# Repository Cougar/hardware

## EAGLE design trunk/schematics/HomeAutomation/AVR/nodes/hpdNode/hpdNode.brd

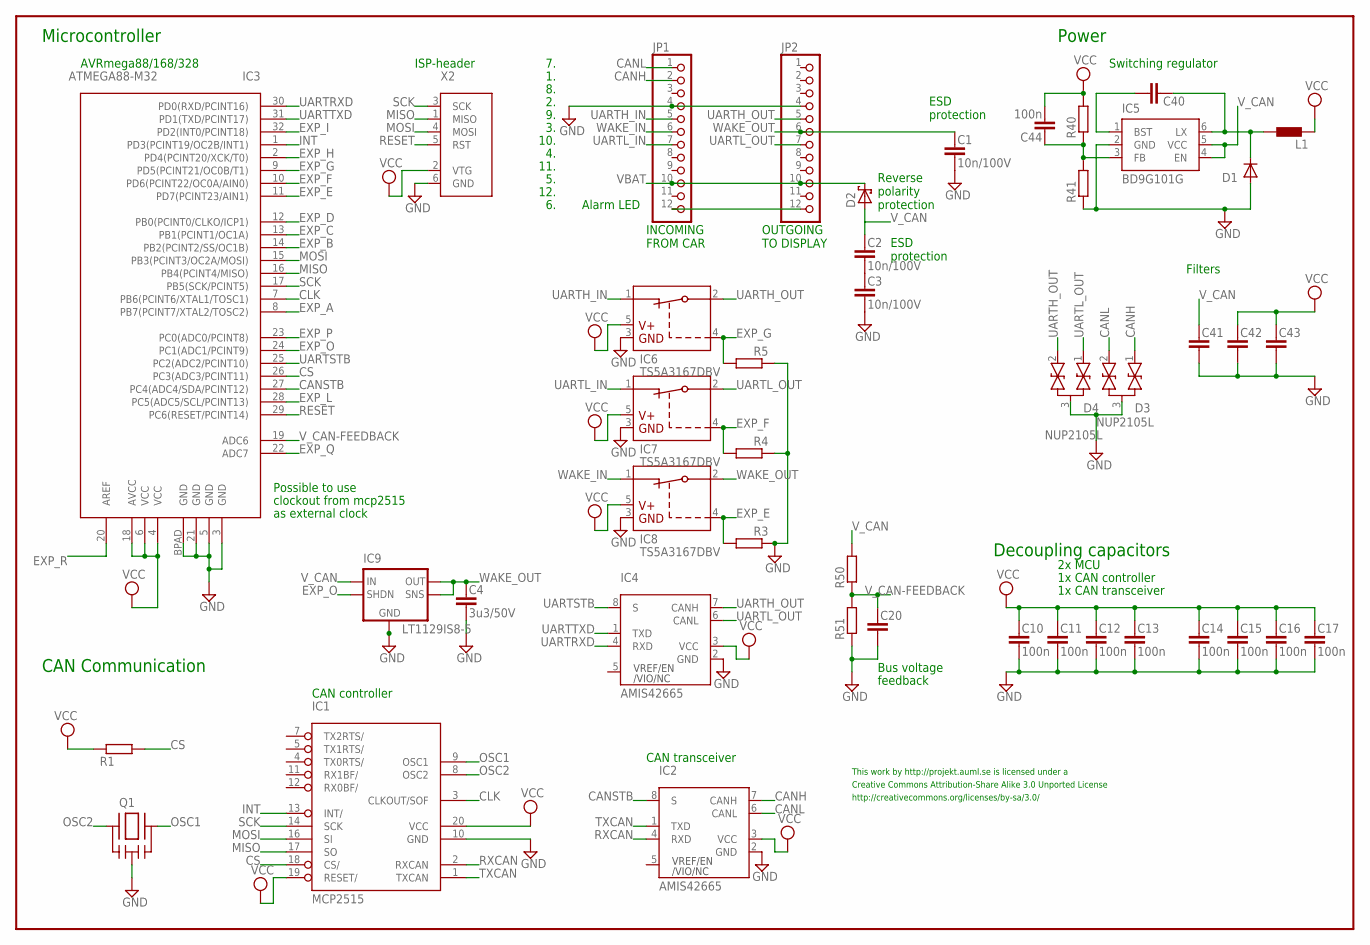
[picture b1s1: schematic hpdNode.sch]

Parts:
C1, C2, C3: 10n/100V; C0805
C4: 3u3/50V; C1210
C10, C11, C12, C13, C14, C15, C16, C17, C44: 100n; C0402
C20, C43: C-EUC0402; C0402
C40: C-EUC0603; C0603
C41: C-EUC1210; C1210
C42: C-EUC0805; C0805
D1: DIODESMP; DO-220AA
D2: SCHOTTKY-DIODESMA; SMA
D3, D4: NUP2105L; SOT23
IC1: MCP2515; TSSOP
IC2, IC4: AMIS42665; SOIC
IC3: ATMEGA88-M32; MLF32
IC5: BD9G101G; SSOP6
IC6, IC7, IC8: TS5A3167DBV; SOT23-5
IC9: LT1129IS8-5; SO8
JP1, JP2: PINHD-2X06; 2X06
L1: L-EUL1210; L1210
Q1: CSTCESMD; SMD
R1, R3, R4, R5, R40, R41, R50, R51: R-EUR0402; R0402
X2: AVRISP6PINHEADER; 6PINHEADER

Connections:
CANH: D3.1, IC2.7 (CANH), JP1.2
CANL: D3.2, IC2.6 (CANL), JP1.1
CANSTB: IC2.8 (S), IC3.27 (PC4(ADC4/SDA/PCINT12))
CB: C40.1, IC5.1 (BST)
CLK: IC1.3 (CLKOUT/SOF), IC3.7 (PB6(PCINT6/XTAL1/TOSC1))
CS: IC1.18 (CS/), IC3.26 (PC3(ADC3/PCINT11)), R1.2
EXP_A: IC3.8 (PB7(PCINT7/XTAL2/TOSC2))
EXP_B: IC3.14 (PB2(PCINT2/SS/OC1B))
EXP_C: IC3.13 (PB1(PCINT1/OC1A))
EXP_D: IC3.12 (PB0(PCINT0/CLKO/ICP1))
EXP_E: IC3.11 (PD7(PCINT23/AIN1)), IC8.4 (IN), R3.2
EXP_F: IC3.10 (PD6(PCINT22/OC0A/AIN0)), IC7.4 (IN), R4.2
EXP_G: IC3.9 (PD5(PCINT21/OC0B/T1)), IC6.4 (IN), R5.2
EXP_H: IC3.2 (PD4(PCINT20/XCK/T0))
EXP_I: IC3.32 (PD2(INT0/PCINT18))
EXP_L: IC3.28 (PC5(ADC5/SCL/PCINT13))
EXP_O: IC3.24 (PC1(ADC1/PCINT9)), IC9.5 (SHDN)
EXP_P: IC3.23 (PC0(ADC0/PCINT8))
EXP_Q: IC3.22 (ADC7)
EXP_R: IC3.20 (AREF)
GND: C1.2, C3.2, C4.2, C10.2, C11.2, C12.2, C13.2, C14.2, C15.2, C16.2, C17.2, C20.2, C41.2, C42.2, C43.2, D1.A, D3.3, D4.3, IC1.10 (GND), IC2.2 (GND), IC3.3 (GND), IC3.5 (GND), IC3.21 (GND), IC3.BPAD (GND), IC4.2 (GND), IC5.2 (GND), IC6.3 (GND), IC7.3 (GND), IC8.3 (GND), IC9.3 (GND), IC9.6 (GND1), IC9.7 (GND2), JP1.4, JP2.4, Q1.2 (GND), R3.1, R4.1, R5.1, R41.1, R51.1, X2.6 (GND)
INT: IC1.13 (INT/), IC3.1 (PD3(PCINT19/OC2B/INT1))
MISO: IC1.17 (SO), IC3.16 (PB4(PCINT4/MISO)), X2.1 (MISO)
MOSI: IC1.16 (SI), IC3.15 (PB3(PCINT3/OC2A/MOSI)), X2.4 (MOSI)
unnamed: C44.1, IC5.3 (FB), R40.1, R41.2
unnamed: C2.2, C3.1
unnamed: JP1.12, JP2.12
OSC1: IC1.9 (OSC1), Q1.3 (2)
OSC2: IC1.8 (OSC2), Q1.1
RESET: IC3.29 (PC6(RESET/PCINT14)), X2.5 (RST)
RXCAN: IC1.2 (RXCAN), IC2.4 (RXD)
SCK: IC1.14 (SCK), IC3.17 (PB5(SCK/PCINT5)), X2.3 (SCK)
TXCAN: IC1.1 (TXCAN), IC2.1 (TXD)
UARTH_IN: IC6.1 (NC), JP1.5
UARTH_OUT: D4.2, IC4.7 (CANH), IC6.2 (COM), JP2.5
UARTL_IN: IC7.1 (NC), JP1.7
UARTL_OUT: D4.1, IC4.6 (CANL), IC7.2 (COM), JP2.7
UARTRXD: IC3.30 (PD0(RXD/PCINT16)), IC4.4 (RXD)
UARTSTB: IC3.25 (PC2(ADC2/PCINT10)), IC4.8 (S)
UARTTXD: IC3.31 (PD1(TXD/PCINT17)), IC4.1 (TXD)
VBAT: D2.C, JP1.10, JP2.10
VCC: C10.1, C11.1, C12.1, C13.1, C14.1, C15.1, C16.1, C17.1, C42.1, C43.1, C44.2, IC1.19 (RESET/), IC1.20 (VCC), IC2.3 (VCC), IC3.4 (VCC), IC3.6 (VCC), IC3.18 (AVCC), IC4.3 (VCC), IC6.5 (VCC), IC7.5 (VCC), IC8.5 (VCC), L1.1, R1.1, R40.2, X2.2 (VTG)
VSW: C40.2, D1.C, IC5.6 (LX), L1.2
V_CAN: C2.1, C41.1, D2.A, IC5.4 (EN), IC5.5 (VCC), IC9.8 (IN), R50.2
V_CAN-FEEDBACK: C20.1, IC3.19 (ADC6), R50.1, R51.2
WAKE_IN: IC8.1 (NC), JP1.6
WAKE_OUT: C1.1, C4.1, IC8.2 (COM), IC9.1 (OUT), IC9.2 (SENSE), JP2.6

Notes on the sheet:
Power
Microcontroller
AVRmega88/168/328
ISP-header
Possible to use
clockout from mcp2515
as external clock
Decoupling capacitors
2x MCU
1x CAN controller
1x CAN transceiver
CAN Communication
Bus voltage
feedback
Switching regulator
Filters
CAN controller
CAN transceiver
This work by http://projekt.auml.se is licensed under a
Creative Commons Attribution-Share Alike 3.0 Unported License
http://creativecommons.org/licenses/by-sa/3.0/
10.
11.
12.
INCOMING FROM CAR
OUTGOING TO DISPLAY
Reverse polarity protection
ESD protection
Alarm LED

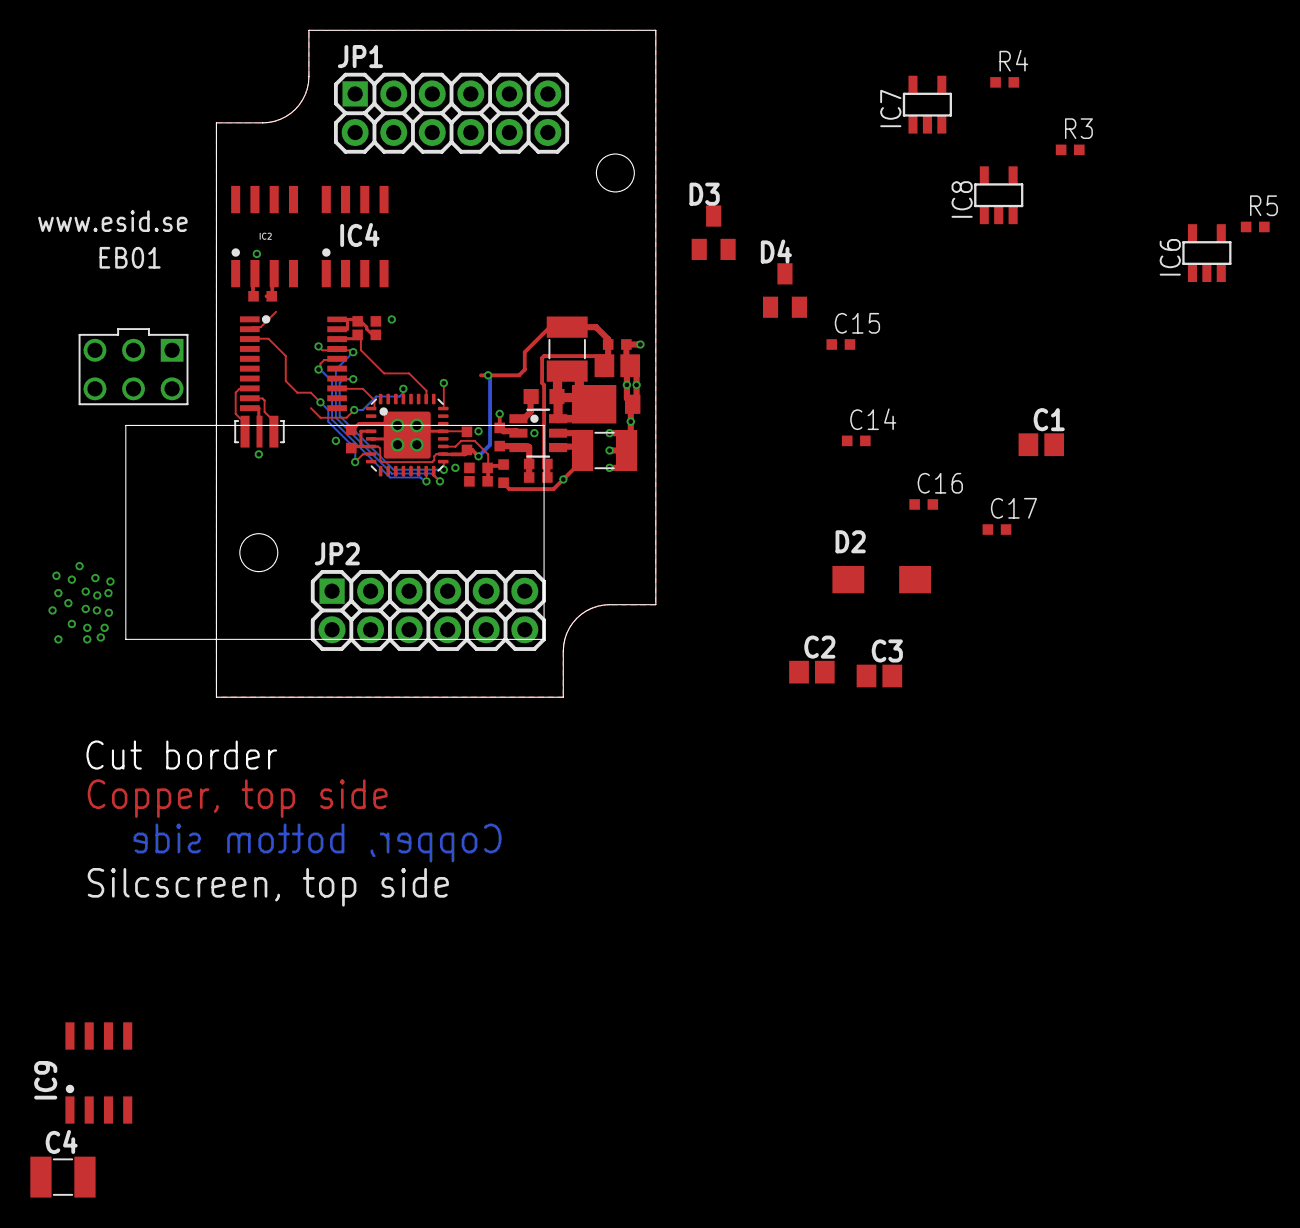
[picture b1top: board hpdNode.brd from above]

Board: 2 copper layers, 34.9 x 43.9 mm, 44 parts (0 on the bottom side), 37 nets.

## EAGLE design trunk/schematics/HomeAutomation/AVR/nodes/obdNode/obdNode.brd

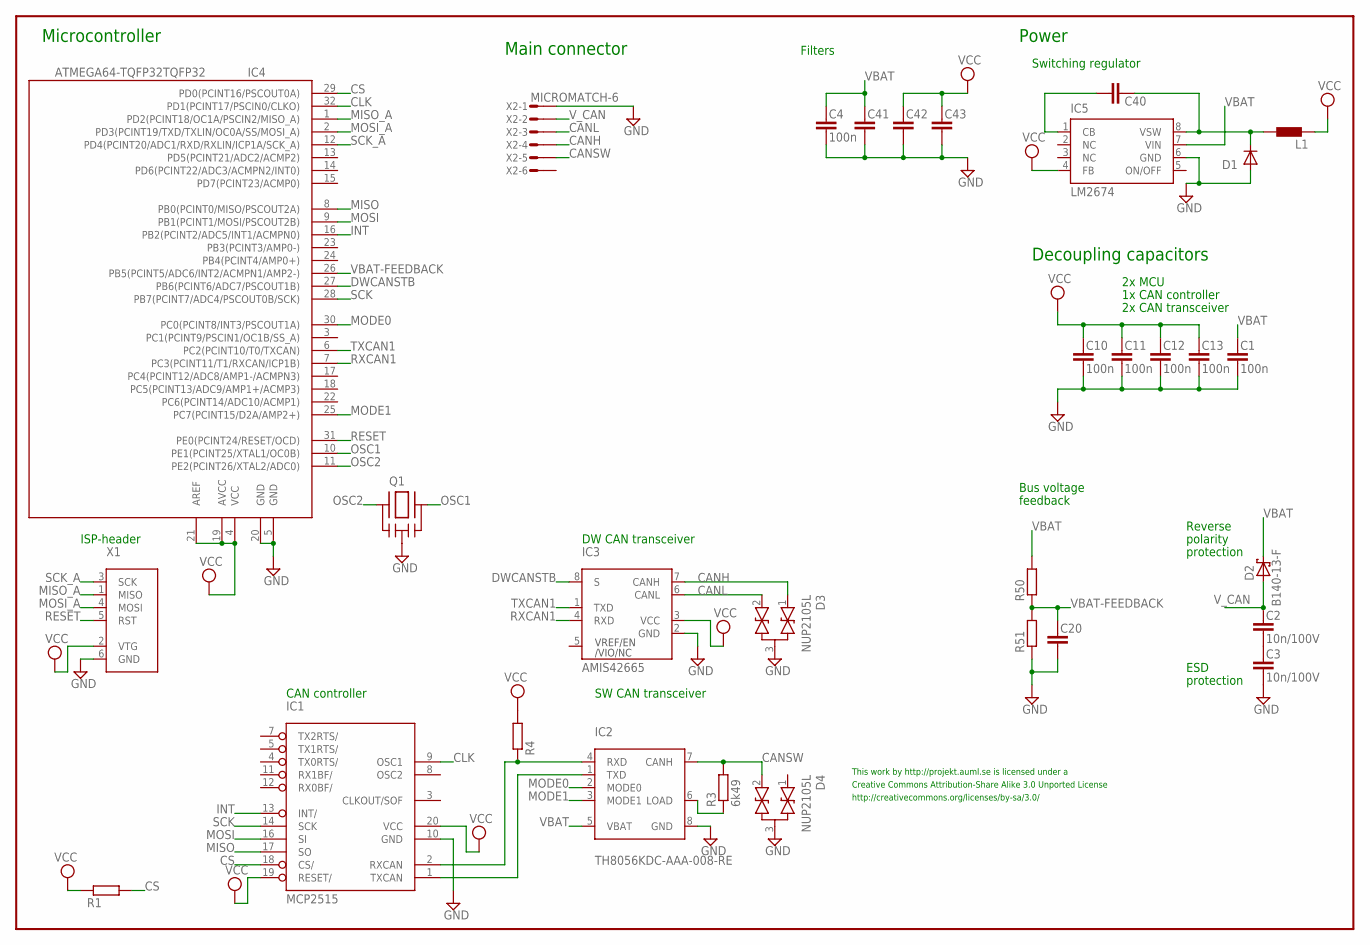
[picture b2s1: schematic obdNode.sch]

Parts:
C1, C4, C10, C11, C12, C13: 100n; C0402
C2, C3: 10n/100V; C0805
C20, C43: C-EUC0402; C0402
C40: C-EUC0603; C0603
C41, C42: C-EUC1210; C1210
D1: DIODESMP; DO-220AA
D2: B140-13-F; SMA
D3, D4: NUP2105L; SOT23
IC1: MCP2515; TSSOP
IC2: TH8056KDC-AAA-008-RE; SOIC
IC3: AMIS42665; SOIC
IC4: ATMEGA64-TQFP32TQFP32; TQFP32
IC5: LM2674; SO8
L1: L-EUL1210; L1210
Q1: CSTCESMD; SMD
R1, R4, R50, R51: R-EUR0402; R0402
R3: 6k49; R0805
X1: AVRISP6PINHEADER; 6PINHEADER
X2: MICROMATCH-6

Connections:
CANH: D3.1, IC3.7 (CANH), X2.4
CANL: D3.2, IC3.6 (CANL), X2.3
CANSW: D4.2, IC2.7 (CANH), R3.2, X2.5
CB: C40.1, IC5.1 (CB)
CLK: IC1.9 (OSC1), IC4.32 (PD1(PCINT17/PSCIN0/CLKO))
CS: IC1.18 (CS/), IC4.29 (PD0(PCINT16/PSCOUT0A)), R1.2
DWCANSTB: IC3.8 (S), IC4.27 (PB6(PCINT6/ADC7/PSCOUT1B))
GND: C1.2, C3.2, C4.2, C10.2, C11.2, C12.2, C13.2, C20.2, C41.2, C42.2, C43.2, D1.A, D3.3, D4.3, IC1.10 (GND), IC2.8 (GND), IC3.2 (GND), IC4.5 (GND), IC4.20 (GND), IC5.6 (GND), Q1.2 (GND), R51.1, X1.6 (GND), X2.1
INT: IC1.13 (INT/), IC4.16 (PB2(PCINT2/ADC5/INT1/ACMPN0))
MISO: IC1.17 (SO), IC4.8 (PB0(PCINT0/MISO/PSCOUT2A))
MISO_A: IC4.1 (PD2(PCINT18/OC1A/PSCIN2/MISO_A)), X1.1 (MISO)
MODE0: IC2.2 (MODE0), IC4.30 (PC0(PCINT8/INT3/PSCOUT1A))
MODE1: IC2.3 (MODE1), IC4.25 (PC7(PCINT15/D2A/AMP2+))
MOSI: IC1.16 (SI), IC4.9 (PB1(PCINT1/MOSI/PSCOUT2B))
MOSI_A: IC4.2 (PD3(PCINT19/TXD/TXLIN/OC0A/SS/MOSI_A)), X1.4 (MOSI)
unnamed: C2.2, C3.1
unnamed: IC2.6 (LOAD), R3.1
OSC1: IC4.10 (PE1(PCINT25/XTAL1/OC0B)), Q1.3 (2)
OSC2: IC4.11 (PE2(PCINT26/XTAL2/ADC0)), Q1.1
RESET: IC4.31 (PE0(PCINT24/RESET/OCD)), X1.5 (RST)
RXCAN1: IC3.4 (RXD), IC4.7 (PC3(PCINT11/T1/RXCAN/ICP1B))
RXCAN2: IC1.2 (RXCAN), IC2.4 (RXD), R4.1
SCK: IC1.14 (SCK), IC4.28 (PB7(PCINT7/ADC4/PSCOUT0B/SCK))
SCK_A: IC4.12 (PD4(PCINT20/ADC1/RXD/RXLIN/ICP1A/SCK_A)), X1.3 (SCK)
TXCAN1: IC3.1 (TXD), IC4.6 (PC2(PCINT10/T0/TXCAN))
TXCAN2: IC1.1 (TXCAN), IC2.1 (TXD)
VBAT: C1.1, C4.1, C41.1, D2.C, IC2.5 (VBAT), IC5.7 (VIN), R50.2
VBAT-FEEDBACK: C20.1, IC4.26 (PB5(PCINT5/ADC6/INT2/ACMPN1/AMP2-)), R50.1, R51.2
VCC: C10.1, C11.1, C12.1, C13.1, C42.1, C43.1, IC1.19 (RESET/), IC1.20 (VCC), IC3.3 (VCC), IC4.4 (VCC), IC4.19 (AVCC), IC4.21 (AREF), IC5.4 (FB), L1.1, R1.1, R4.2, X1.2 (VTG)
VSW: C40.2, D1.C, IC5.8 (VSW), L1.2
V_CAN: C2.1, D2.A, X2.2

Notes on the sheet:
Power
Microcontroller
ISP-header
Decoupling capacitors
2x MCU
1x CAN controller
2x CAN transceiver
Bus voltage
feedback
Switching regulator
Filters
CAN controller
DW CAN transceiver
This work by http://projekt.auml.se is licensed under a
Creative Commons Attribution-Share Alike 3.0 Unported License
http://creativecommons.org/licenses/by-sa/3.0/
Reverse
protection
polarity
ESD
Main connector
SW CAN transceiver

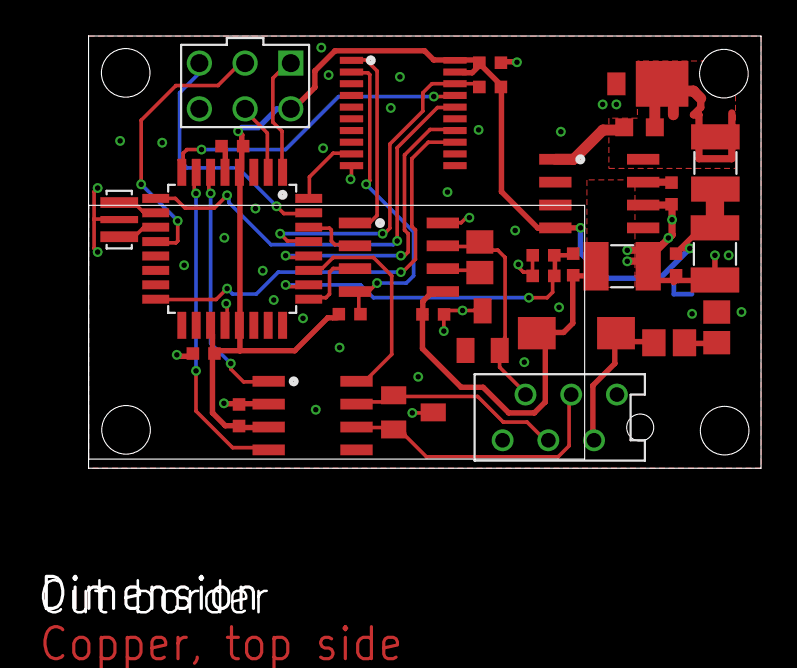
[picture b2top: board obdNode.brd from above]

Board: 2 copper layers, 37.4 x 24.0 mm, 31 parts (0 on the bottom side), 31 nets.

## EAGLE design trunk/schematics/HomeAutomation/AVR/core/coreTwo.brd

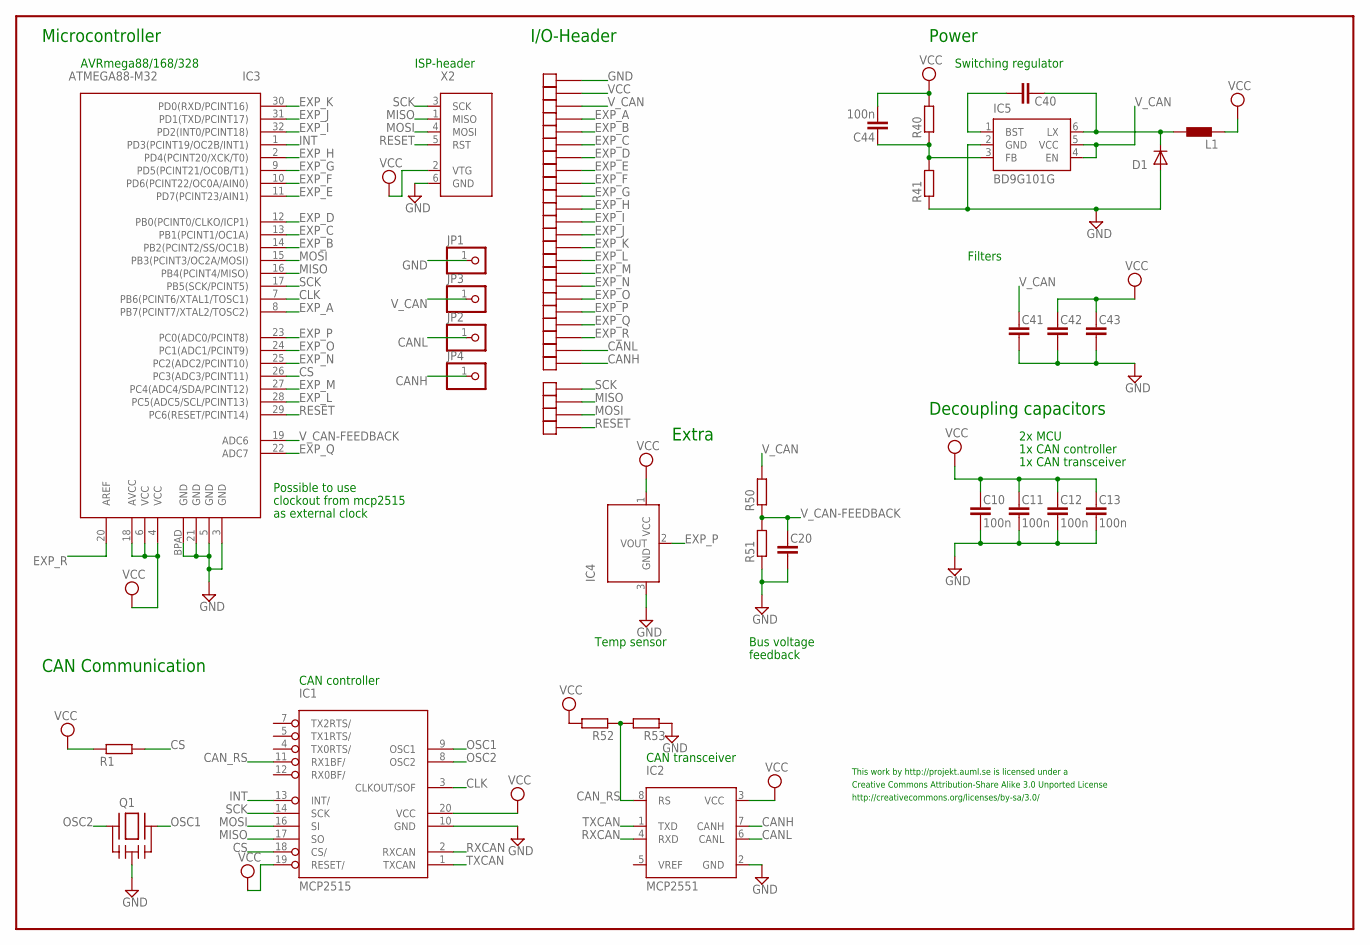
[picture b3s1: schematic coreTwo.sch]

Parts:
C10, C11, C12, C13, C44: 100n; C0402
C20, C43: C-EUC0402; C0402
C40: C-EUC0603; C0603
C41: C-EUC1210; C1210
C42: C-EUC0805; C0805
CANH: CORETWO_PIN
CANL: CORETWO_PIN
D1: DIODESMP; DO-220AA
EXP_A: CORETWO_PIN
EXP_B: CORETWO_PIN
EXP_C: CORETWO_PIN
EXP_D: CORETWO_PIN
EXP_E: CORETWO_PIN
EXP_F: CORETWO_PIN
EXP_G: CORETWO_PIN
EXP_H: CORETWO_PIN
EXP_I: CORETWO_PIN
EXP_J: CORETWO_PIN
EXP_K: CORETWO_PIN
EXP_L: CORETWO_PIN
EXP_M: CORETWO_PIN
EXP_N: CORETWO_PIN
EXP_O: CORETWO_PIN
EXP_P: CORETWO_PIN
EXP_Q: CORETWO_PIN
EXP_R: CORETWO_PIN
GND: CORETWO_PIN
IC1: MCP2515; TSSOP
IC2: MCP2551; SOIC
IC3: ATMEGA88-M32; MLF32
IC4: TC1047A; SOT23
IC5: BD9G101G; SSOP6
JP1, JP2, JP3, JP4: PINHD-1X1SMD; 1X01_SMD
L1: L-EUL1210; L1210
MISO: CORETWO_PIN
MOSI: CORETWO_PIN
Q1: CSTCESMD; SMD
R1, R40, R41, R50, R51, R52, R53: R-EUR0402; R0402
RST: CORETWO_PIN
SCK: CORETWO_PIN
VCC: CORETWO_PIN
V_CAN: CORETWO_PIN
X2: AVRISP6PIN; 6PINSMD

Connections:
CANH: CANH.1, IC2.7 (CANH), JP4.1
CANL: CANL.1, IC2.6 (CANL), JP2.1
CAN_RS: IC1.11 (RX1BF/), IC2.8 (RS), R52.1, R53.2
CB: C40.1, IC5.1 (BST)
CLK: IC1.3 (CLKOUT/SOF), IC3.7 (PB6(PCINT6/XTAL1/TOSC1))
CS: IC1.18 (CS/), IC3.26 (PC3(ADC3/PCINT11)), R1.2
EXP_A: EXP_A.1, IC3.8 (PB7(PCINT7/XTAL2/TOSC2))
EXP_B: EXP_B.1, IC3.14 (PB2(PCINT2/SS/OC1B))
EXP_C: EXP_C.1, IC3.13 (PB1(PCINT1/OC1A))
EXP_D: EXP_D.1, IC3.12 (PB0(PCINT0/CLKO/ICP1))
EXP_E: EXP_E.1, IC3.11 (PD7(PCINT23/AIN1))
EXP_F: EXP_F.1, IC3.10 (PD6(PCINT22/OC0A/AIN0))
EXP_G: EXP_G.1, IC3.9 (PD5(PCINT21/OC0B/T1))
EXP_H: EXP_H.1, IC3.2 (PD4(PCINT20/XCK/T0))
EXP_I: EXP_I.1, IC3.32 (PD2(INT0/PCINT18))
EXP_J: EXP_J.1, IC3.31 (PD1(TXD/PCINT17))
EXP_K: EXP_K.1, IC3.30 (PD0(RXD/PCINT16))
EXP_L: EXP_L.1, IC3.28 (PC5(ADC5/SCL/PCINT13))
EXP_M: EXP_M.1, IC3.27 (PC4(ADC4/SDA/PCINT12))
EXP_N: EXP_N.1, IC3.25 (PC2(ADC2/PCINT10))
EXP_O: EXP_O.1, IC3.24 (PC1(ADC1/PCINT9))
EXP_P: EXP_P.1, IC3.23 (PC0(ADC0/PCINT8)), IC4.2 (VOUT)
EXP_Q: EXP_Q.1, IC3.22 (ADC7)
EXP_R: EXP_R.1, IC3.20 (AREF)
GND: C10.2, C11.2, C12.2, C13.2, C20.2, C41.2, C42.2, C43.2, D1.A, GND.1, IC1.10 (GND), IC2.2 (GND), IC3.3 (GND), IC3.5 (GND), IC3.21 (GND), IC3.BPAD (GND), IC4.3 (GND), IC5.2 (GND), JP1.1, Q1.2 (GND), R41.1, R51.1, R53.1, X2.6 (GND)
INT: IC1.13 (INT/), IC3.1 (PD3(PCINT19/OC2B/INT1))
MISO: IC1.17 (SO), IC3.16 (PB4(PCINT4/MISO)), MISO.1, X2.1 (MISO)
MOSI: IC1.16 (SI), IC3.15 (PB3(PCINT3/OC2A/MOSI)), MOSI.1, X2.4 (MOSI)
unnamed: C44.1, IC5.3 (FB), R40.1, R41.2
OSC1: IC1.9 (OSC1), Q1.3 (2)
OSC2: IC1.8 (OSC2), Q1.1
RESET: IC3.29 (PC6(RESET/PCINT14)), RST.1, X2.5 (RST)
RXCAN: IC1.2 (RXCAN), IC2.4 (RXD)
SCK: IC1.14 (SCK), IC3.17 (PB5(SCK/PCINT5)), SCK.1, X2.3 (SCK)
TXCAN: IC1.1 (TXCAN), IC2.1 (TXD)
VCC: C10.1, C11.1, C12.1, C13.1, C42.1, C43.1, C44.2, IC1.19 (RESET/), IC1.20 (VCC), IC2.3 (VCC), IC3.4 (VCC), IC3.6 (VCC), IC3.18 (AVCC), IC4.1 (VCC), L1.1, R1.1, R40.2, R52.2, VCC.1, X2.2 (VTG)
VSW: C40.2, D1.C, IC5.6 (LX), L1.2
V_CAN: C41.1, IC5.4 (EN), IC5.5 (VCC), JP3.1, R50.2, V_CAN.1
V_CAN-FEEDBACK: C20.1, IC3.19 (ADC6), R50.1, R51.2

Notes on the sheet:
Power
Microcontroller
AVRmega88/168/328
ISP-header
Possible to use
clockout from mcp2515
as external clock
Decoupling capacitors
2x MCU
1x CAN controller
1x CAN transceiver
CAN Communication
I/O-Header
Extra
Bus voltage
feedback
Switching regulator
Filters
CAN controller
CAN transceiver
This work by http://projekt.auml.se is licensed under a
Creative Commons Attribution-Share Alike 3.0 Unported License
http://creativecommons.org/licenses/by-sa/3.0/
Temp sensor

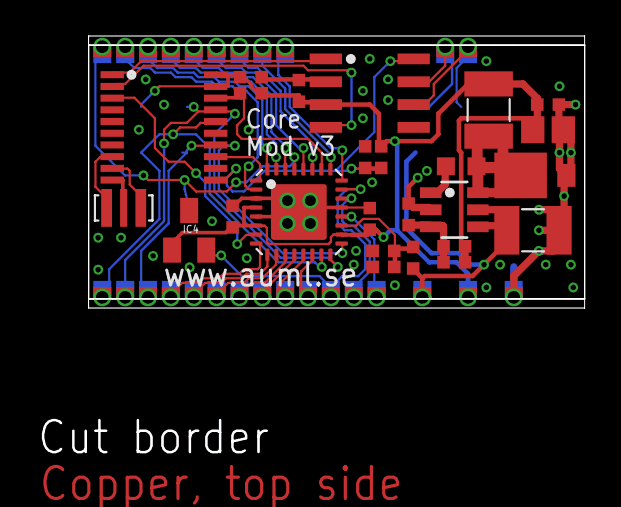
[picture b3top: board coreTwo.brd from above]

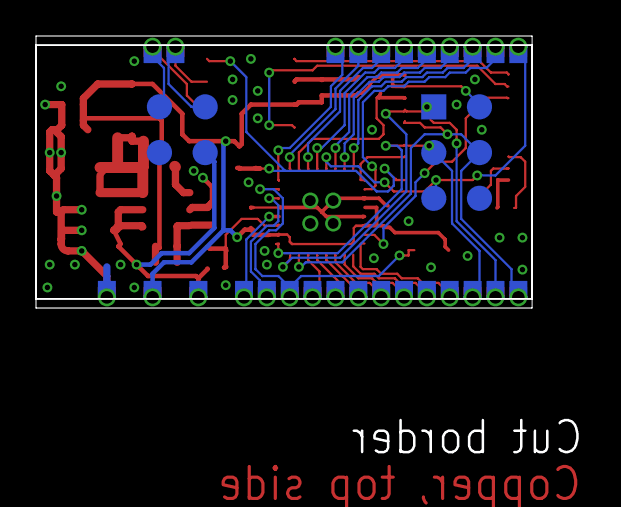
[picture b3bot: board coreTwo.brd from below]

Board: 2 copper layers, 27.6 x 15.1 mm, 57 parts (4 on the bottom side), 39 nets.

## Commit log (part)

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2008-07-10 removed BusIsolator, not a valid design
2008-07-11 Updated components
2008-07-11 dimmer: fixed a problem with generating svnimage to wiki
2008-07-12 expansion/dimmer: first draft of schematic and board. Only 2 channels, third channel will be added after design validation.
2008-07-12 Added and updated some components for the dimmer core expansion
2008-07-12 nodes/isolated: changed adum-library library: removed adum.lbr
2008-07-13 dimmer: deleted three-channel, added one-channel single layer with fuse
2008-07-13 dimmer: minor tweaks
2008-07-16 dimmer: reverted changes on schmittrigger
2008-08-02 Finished routeing on RGBWdriverModule
2008-08-02 core-expansions/template: better helptext for the I/O-header
2008-08-03 coreexpansions/template: changed default grid to 10 mil from 1 mil
2008-08-04 coreexpansions/RGBdriverModule: OPamp-variant routing done
2008-08-04 Current monitor used in RGBW_Driver
2008-08-04 library/inductor: fixed silcscreen
2008-08-04 coreexpansion/RGBdriverModule: minor changes for opamp-version
2008-08-05 coreexpansions/RGBdriverModule: opamp-variant cleanup, fixes
2008-08-06 coreexpansions/usb: added title on silc
2008-08-06 coreexpansions/simpleDTMF: minor changes
2008-08-06 coreexpansions: renaming and silc
2008-08-06 coreexpansions/cLCD: added url, title and version
2008-08-06 coreexpansions/gLCD: added cap on vcc for display
2008-08-06 coreexpansion/RGBWdriver: changed name of inductors
2008-08-06 Updated lib with male-pcb connector
2008-08-06 Fixed some more errors
2008-08-06 updated micromatch lib and 4-way-corecard
2008-08-06 coreexpansions/RGBWdriver: added feedback for measuring power supply voltage
2008-08-07 coreexp/RGBWdriver: added pulldown on transistor gates, moved adcs to be able to use temp sensor on corecard
2008-08-09 coreexp/RGBWdriver: minor fixes
2008-08-10 expansions/remotecontrol: renamed schematic and board file
2008-08-10 expansions/remotecontrol: added rf receiver, finish
2008-08-16 coreexpansions/dimmer230: added minor silc
2008-08-17 RGBWdriver: added gate resistor
2008-08-23 coreexpansions/rs232: made a new layout for double side, the old single side variant is called rs232.singleside
2008-08-24 rs232: minor fixes
2008-08-26 Added 6-pin pinheader for connection of touch-panel or SPI interface
2008-08-27 dimmer230: minor fixes
2008-09-09 coreexpansions: added schematic for external can, use with corecard for can-gateway or use with another platform (arm...), 3.3V- and 5V-compatible
2008-09-09 coreexp/can: added brd with preliminary component layout
2008-09-10 coreexp/extcan: component placement almost done
2008-09-13 coreexpansions/expcan: routing complete
2008-09-14 extcan: minor changes
2008-09-21 eagle/library: added opamp and modified pinhead-mm
2008-09-23 expansions/simpleethernet: fixed review comment
2008-09-23 expansions/cLCD: updated after review, fixed jumper for backlight voltage and silc for pin1 on pinheaders
2008-09-24 expansions/dimmer: changed external interface to micromatch, changed opto-triac-driver to smd package library: added smd opto-triac-driver, updated micromatch
2008-09-24 expansions/dimmer: changed pins for external interface
2008-09-24 expansion/biggenericpwm: reverted to old version due to restrictions with later versions of eagle
2008-09-24 expansions/biggenericpwm: fixed comments from review, polygon fixes and gnd vias near big capacitors.
2008-09-24 expansion/RGBWdriver: updates after review, fixed overlap between inductors and skruvplintar
2008-10-01 expansion/dimmer: changed resistor values
2008-10-08 Touch-exp: added early design to svn, micromatch and zifconnector currently
2008-10-10 touch-exp: minor changes
2008-10-11 expansion/dimmer: added varistor for protection
2008-10-12 Lib for the Avago HSMF-C113 rgb diode
2008-10-19 expansion/rgbwdriver: moved silctext from copper
2008-10-21 library/avago RGBLED: fixed symbol grid
2008-10-22 touch-exp: last changes library/avago-led: fixes
2008-10-22 touch-exp: routing avago-led: fix silc
2008-10-25 expansion/remotecontrol: moved ir receivers to the edge library/ir receivers: moved silc to tdocu
2008-10-25 library: added fusefolder for dimmer
2008-11-02 Updates after olimex-order expansions: moved ioheader silc to tdocu dimmer/touch: updated the micromatch-connector simpledtmf: fixed silc (url/name/ver)
2008-11-25 4way-corecard: added descriptive silc for power supply connector, made power track wider
2008-11-30 expansion/dimmer230, updates since test-order: layout changes, removed switch feedback, placed two resistors in serie where needed, rotated mains and load connectors
2008-12-06 expansion/simpleDTMF: changed dtmf-decoder to smd variant
2008-12-07 added subfolder to revision 4
2008-12-07 Minor silc fixes on 4way
2008-12-07 removed 4way in tags
2008-12-07 copy usb expansion to tags
2008-12-07 copy remote control expansion to tags
2008-12-07 expansions/ethernet: added reference layer with component placement
2008-12-08 expansions/ethernet: changed silc for myro order
2008-12-10 hardware freeze for expansion order, part 1
2008-12-10 updates of expansions before freez, changes: silcscreen and component placement layer
2008-12-10 all expansions: changed some drc settings for via holes
2008-12-13 tags/revision4: added pngs for all expansions and pdf for ethernet
2008-12-14 expansions: added corecard tester, schematic and layout finished
2009-01-19 test svn:ignore properties on *.s#* and *.b#* (eagle backup files)
2009-01-24 cLCD: fixes for BL and 4-bit mode
2009-01-24 library: fixed holes rotary encoder expansions/cLCD: updated component rotary encoder
2009-01-24 expansion/dimmer: fixed copper at mounting hole, moved mains connector some mm, moved R14, added 7.5-hole for C2
2009-01-25 expansions/rgbwdriver: updated silc and vias size, no reference layer for component placement yet
2009-01-27 expansions/dimmer: renamed net and placed the name in the schematic
2009-01-29 expansion/dtmf: new layout expansion: glcd and dimmer, minor updates and changes for myro-order
2009-01-29 touch-exp: updated for order
2009-01-31 added test order to tags
2009-02-01 tags: added revision4b with simpleDTMF, cLCD, gLCD, RGBdriverModule, dimmer and Touch-exp. postprocessing and image exports missing
2009-02-02 tags: added gerbers and pngs
2009-02-04 tags/dimmer: minor fixes to bom
2009-02-08 expansions/teleCommunication: added function block diagram (.dia) and the template schematic and board
2009-02-09 expansion/template: added function.dia template
2009-02-09 expansion/remotecontrol: minor fix to functional overview
2009-02-10 expansion: updated functional overviews again
2009-02-10 expansions/simpleDTMF: added functional overview
2009-02-14 minor change to microchip.lbr (component layout for eeprom corrected)
2009-02-15 expansions: functional blocks for usb and simpleethernet again
2009-02-15 corecard functional block
2009-06-09 corecard/functional diagram: changed CAN to CAN & Power on wire
2009-07-24 expansions/expCard: Made card one row wider, fixed tstop/bstop, now connected aref
2009-07-25 expansions: commit to generate image files for missing boards
2009-07-29 telecommunication: more work in schematic, commit for comments
2009-07-29 telecommunication-expansion: final updated before leaving for gbg
2009-07-31 telecomm: changed two sot23-zener to one sot23-tvs according to eqlazers suggestion
2009-09-03 coreModule: routing started
2009-09-07 Fixed problems with crashing eagle (ABORT: Unknown objectType) (maybe), and tried to restore changes since last commit: added component placement layer in references
2009-09-08 library: added more parts/packages to expboard, avrisp, pinhead-mm, rcl and atmega88
2009-09-21 tags: added revision5 with core2 (coremodule)
2009-09-22 coreAdapter: added io-area as linus suggestion
2009-10-05 coreTwo: mirrored smd-isp
2009-11-03 Updated coreTwo with new inductance and also lib rcl
2009-11-07 tags/coreAdapter added
2009-11-11 coreModule: minor silc fix
2009-11-23 Minor library updates
2010-01-01 Added board testerProgHeader, suppose to be used when creating ISP rigs for programming without soldering a pin header
2010-01-04 testerProgHeader: added some slic, ready for order
2010-01-22 added resonator to lib, updated led.lbr, updated coreModule with the resonator (pitch was wrong, 1.2mm->0.95mm)
2010-04-09 Now the simulation looks good...
2010-04-11 New OPAMP used
2010-04-12 new RGBw-module, with analog current control
2010-05-27 added USB expansion for coremodule, minor work done
2010-06-03 core module: added voltage divider for switched psu, to be able to use adjustable variant
2010-06-06 minor changes to rcl.lbr
2010-08-07 led.lbr: added layout for new LED
2010-09-15 coremodule: tagged new bom
2010-09-15 core module: updated tagged bom with voltage for 100n
2010-09-20 expansion USB: save document before commit... minor fix in tagged BOM
2010-10-16 added tagged modexpUSB
2010-10-16 tagged coreTwo
2010-10-16 added sch and brd for tagged coreTwo
2011-02-28 Added first draft of RBGW-driver for coreModule
2011-02-28 Removed temporary eagle files that accidently got commited
2011-03-01 More routeing done, still some left and the comparator must be changed (to expensive) maight be better to use a bipolar tranistor instead of the mosfets?
2011-03-10 Added new dtmf module expansion, based on work done in telecommunication expansion but removed some features.
2011-04-22 First layout of RGBW
2011-04-25 Fixed angle routing
2011-04-25 Added panel for prototype order
2011-05-01 Added BOM list to RGBW-driver
2011-08-28 More work done on dot matrix design, also updated a few libraries and added led-matrix.lbr
2011-08-29 Added edge pinheader in dot matrix again, could be useful
2011-08-30 Added url for prototyp order to schematic
2011-08-30 Schematic almost completed, minor component placement done
2011-08-31 Added template function.dia for all mod expansions including template
2011-09-01 Added driver TD62083 (uln compatible)
2011-09-03 Updated function.dia for dotmatrix expansion
2011-09-03 Minor fix to function.dia for dotmatrix
2011-09-08 Started routing of dotmatrix module Minor placement fix on led-matrix lib
2011-09-12 Minor routing fixes
2011-09-12 Moved prototype order to tags
2011-09-16 Added note about adding external power supply
2011-09-18 Minor optimization
2011-11-17 Added 1x10 pinheader lib
2011-11-17 Added R2512 to rcl
2011-11-17 Added ffc connector
2012-05-19 Converted coremod image to objects due to dia not embedding images
2012-05-20 Updated function dia for core adapter New hack: IR rx
2012-05-20 Reverted color
2012-05-20 Reverted color on ir tx hack
2012-05-22 Added hack for led detector, useful for power meter measure
2012-05-22 New try filling holes
2012-05-25 Minor fixes to hardware hacks
2012-06-09 First draft of Qtouch schematics, still routing to do
2012-06-10 Removed Qtouch from template
2012-06-10 More rounting done
2012-06-15 Added tag for new order of qtouch, coreadapter and 6way
2012-06-15 Added sch and brd for 6way to tag
2012-06-18 moved revision9combined into revision9
2012-08-14 Added hack for opto switch Minor change in led detector
2012-10-22 Added revision10, coreadapter+6way+4way
2012-10-23 Added 4-way .com file updated .cam for coreAdapter Updated GerbmergeConfig with 4-way
2012-11-12 More work on android gateway
2012-11-24 Added ESD-protection on CAN, transient and reverse protection on power supply
2012-11-25 Added lib choke.lbr, minor fix in usba.lbr Android-gw schematic done, component layout started
2012-12-03 Minor fixes in android gateway
2012-12-04 Added mounting holes on PCB
2012-12-11 Updated functional diagram
2012-12-11 Added empty folder for Gerbers, added cam for android
2012-12-11 Created revision 11 tag
2012-12-11 Added board name to silcscreen
2012-12-11 Last commit, once again
2012-12-13 Added mlx90614 infrared thermometer
2012-12-16 Thermometer component placement and routing done
2012-12-17 Rotated micromatch connector on thermo boards
2012-12-21 Added PCB name
2013-02-28 Added new tester programming header for PCB test points
2013-05-09 Added pho odb-connector modexpansion and some cam files
2014-04-02 Added obdNode, currently just a copy of coremodule
2014-04-03 Added new DW-CAN transceiver More work on nodeObd
2014-04-06 nodeObd schematic finished
2014-04-07 Added resonator for obdNode
2014-04-13 Fixes on placement
2014-05-03 Minor layout improvements
2015-01-13 Updated version of core module with - a cheaper PSU - ISP-contacts as board-edge-connectors
2015-09-10 Renamed libs with uppercase letters to lowercase Added analog switch ts5a3167
2015-09-10 Added GND, V+ texts in symbol
